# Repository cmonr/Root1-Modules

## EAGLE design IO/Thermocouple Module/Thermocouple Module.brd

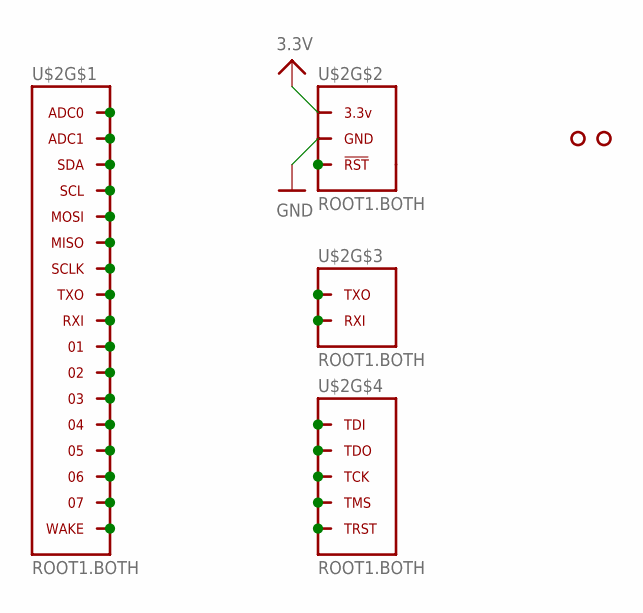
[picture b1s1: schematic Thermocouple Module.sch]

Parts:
U$2: ROOT1.BOTH
U$3, U$4: HOLE.2MM; 2MM

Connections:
3.3V: U$2.3.3V@1 (3.3V), U$2.3.3V@2 (3.3V), U$2.3.3V@3 (3.3V), U$2.3.3V@4 (3.3V), U$2.3.3V@5 (3.3V), U$2.3.3V@6 (3.3V), U$2.3.3V@7 (3.3V), U$2.3.3V@8 (3.3V), U$2.3.3V@9 (3.3V), U$2.3.3V@10 (3.3V), U$2.3.3V@11 (3.3V), U$2.3.3V@12 (3.3V), U$2.3.3V@13 (3.3V), U$2.3.3V@14 (3.3V), U$2.3.3V@15 (3.3V), U$2.3.3V@16 (3.3V), U$2.3.3V@17 (3.3V), U$2.3.3V@18 (3.3V), U$2.3.3V@19 (3.3V), U$2.3.3V@20 (3.3V), U$2.3.3V@21 (3.3V), U$2.3.3V@22 (3.3V), U$2.3.3V@23 (3.3V), U$2.3.3V@24 (3.3V), U$2.3.3V@VIA (3.3V)
GND: U$2.GND@1 (GND), U$2.GND@2 (GND), U$2.GND@3 (GND), U$2.GND@4 (GND), U$2.GND@5 (GND), U$2.GND@6 (GND), U$2.GND@7 (GND), U$2.GND@8 (GND), U$2.GND@9 (GND), U$2.GND@10 (GND), U$2.GND@11 (GND), U$2.GND@12 (GND), U$2.GND@13 (GND), U$2.GND@14 (GND), U$2.GND@15 (GND), U$2.GND@16 (GND), U$2.GND@17 (GND), U$2.GND@18 (GND), U$2.GND@19 (GND), U$2.GND@20 (GND), U$2.GND@21 (GND), U$2.GND@22 (GND), U$2.GND@23 (GND), U$2.GND@24 (GND), U$2.GND@25 (GND), U$2.GND@26 (GND), U$2.GND@VIA (GND)
unnamed: U$2.04, U$2.04@1 (04), U$2.04@VIA (04)
unnamed: U$2.ADC1, U$2.ADC1@1 (ADC1), U$2.ADC1@VIA (ADC1)
unnamed: U$2.SDA, U$2.SDA@1 (SDA), U$2.SDA@VIA (SDA)
unnamed: U$2.SCL, U$2.SCL@1 (SCL), U$2.SCL@VIA (SCL)
unnamed: U$2.03, U$2.03@1 (03), U$2.03@VIA (03)
unnamed: U$2.MISO, U$2.MISO@1 (MISO), U$2.MISO@VIA (MISO)
unnamed: U$2.SCLK, U$2.SCLK@1 (SCLK), U$2.SCLK@VIA (SCLK)
unnamed: U$2.TXO, U$2.TXO@1 (TXO), U$2.TXO@VIA (TXO)
unnamed: U$2.RXI, U$2.RXI@1 (RXI), U$2.RXI@VIA (RXI)
unnamed: U$2.01, U$2.01@1 (01), U$2.01@VIA (01)
unnamed: U$2.02, U$2.02@1 (02), U$2.02@VIA (02)
unnamed: U$2.MOSI, U$2.MOSI@1 (MOSI), U$2.MOSI@VIA (MOSI)
unnamed: U$2.ADC0, U$2.ADC0@1 (ADC0), U$2.ADC0@VIA (ADC0)
unnamed: U$2.05, U$2.05@1 (05), U$2.05@VIA (05)
unnamed: U$2.06, U$2.06@1 (06), U$2.06@VIA (06)
unnamed: U$2.07, U$2.07@1 (07), U$2.07@VIA (07)
unnamed: U$2.WAKE, U$2.WAKE@1 (WAKE), U$2.WAKE@VIA (WAKE)
unnamed: U$2.TDI, U$2.TDI@1 (TDI), U$2.TDI@VIA (TDI)
unnamed: U$2.TDO, U$2.TDO@1 (TDO), U$2.TDO@VIA (TDO)
unnamed: U$2.TCK, U$2.TCK@1 (TCK), U$2.TCK@VIA (TCK)
unnamed: U$2.TMS, U$2.TMS@1 (TMS), U$2.TMS@VIA (TMS)
unnamed: U$2.TRST, U$2.TRST@1 (TRST), U$2.TRST@VIA (TRST)
unnamed: U$2.RXI.DBG (RXI), U$2.RXI.DBG@1 (RXI), U$2.RXI.DBG@VIA (RXI)
unnamed: U$2.TXO.DBG (TXO), U$2.TXO.DBG@1 (TXO), U$2.TXO.DBG@VIA (TXO)
unnamed: U$2.RST (!RST), U$2.RST@1 (!RST), U$2.RST@VIA (!RST)

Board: 2 copper layers, 3 parts (0 on the bottom side), 27 nets, no tracks yet.

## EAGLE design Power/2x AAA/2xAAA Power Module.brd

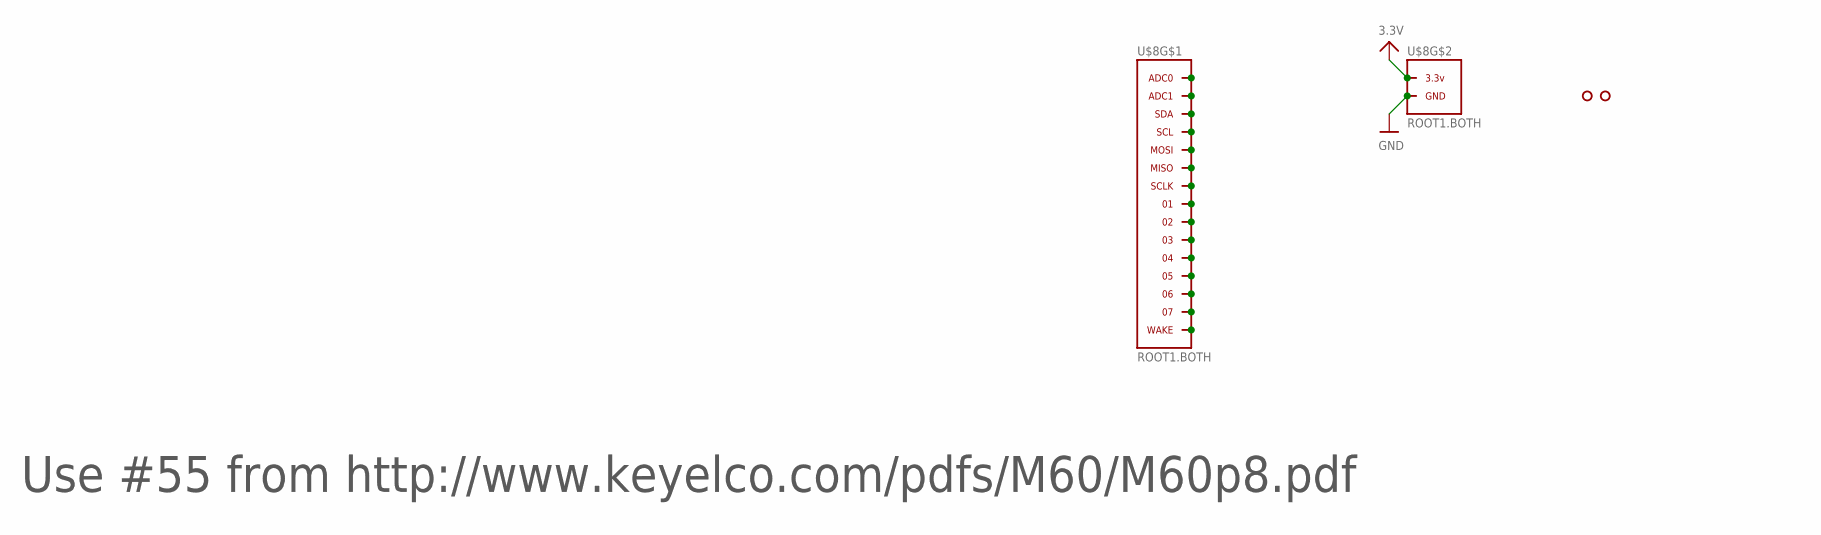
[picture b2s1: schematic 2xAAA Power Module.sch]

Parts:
U$3, U$4: HOLE.2MM; 2MM
U$8: ROOT1.BOTH

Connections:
3.3V: U$8.3.3V@1 (3.3V), U$8.3.3V@2 (3.3V), U$8.3.3V@3 (3.3V), U$8.3.3V@4 (3.3V), U$8.3.3V@5 (3.3V), U$8.3.3V@6 (3.3V), U$8.3.3V@7 (3.3V), U$8.3.3V@8 (3.3V), U$8.3.3V@9 (3.3V), U$8.3.3V@10 (3.3V), U$8.3.3V@VIA (3.3V)
GND: U$8.GND@1 (GND), U$8.GND@2 (GND), U$8.GND@3 (GND), U$8.GND@4 (GND), U$8.GND@5 (GND), U$8.GND@6 (GND), U$8.GND@7 (GND), U$8.GND@8 (GND), U$8.GND@9 (GND), U$8.GND@10 (GND), U$8.GND@11 (GND), U$8.GND@12 (GND), U$8.GND@13 (GND), U$8.GND@14 (GND), U$8.GND@15 (GND), U$8.GND@16 (GND), U$8.GND@17 (GND), U$8.GND@18 (GND), U$8.GND@19 (GND), U$8.GND@20 (GND), U$8.GND@VIA (GND)
unnamed: U$8.ADC0, U$8.ADC0@1 (ADC0), U$8.ADC0@VIA (ADC0)
unnamed: U$8.ADC1, U$8.ADC1@1 (ADC1), U$8.ADC1@VIA (ADC1)
unnamed: U$8.SDA, U$8.SDA@1 (SDA), U$8.SDA@VIA (SDA)
unnamed: U$8.SCL, U$8.SCL@1 (SCL), U$8.SCL@VIA (SCL)
unnamed: U$8.MOSI, U$8.MOSI@1 (MOSI), U$8.MOSI@VIA (MOSI)
unnamed: U$8.MISO, U$8.MISO@1 (MISO), U$8.MISO@VIA (MISO)
unnamed: U$8.SCLK, U$8.SCLK@1 (SCLK), U$8.SCLK@VIA (SCLK)
unnamed: U$8.01, U$8.01@1 (01), U$8.01@VIA (01)
unnamed: U$8.02, U$8.02@1 (02), U$8.02@VIA (02)
unnamed: U$8.03, U$8.03@1 (03), U$8.03@VIA (03)
unnamed: U$8.04, U$8.04@1 (04), U$8.04@VIA (04)
unnamed: U$8.05, U$8.05@1 (05), U$8.05@VIA (05)
unnamed: U$8.06, U$8.06@1 (06), U$8.06@VIA (06)
unnamed: U$8.07, U$8.07@1 (07), U$8.07@VIA (07)
unnamed: U$8.WAKE, U$8.WAKE@1 (WAKE), U$8.WAKE@VIA (WAKE)

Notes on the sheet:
Use #55 from http://www.keyelco.com/pdfs/M60/M60p8.pdf

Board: 2 copper layers, 3 parts (0 on the bottom side), 17 nets, no tracks yet.

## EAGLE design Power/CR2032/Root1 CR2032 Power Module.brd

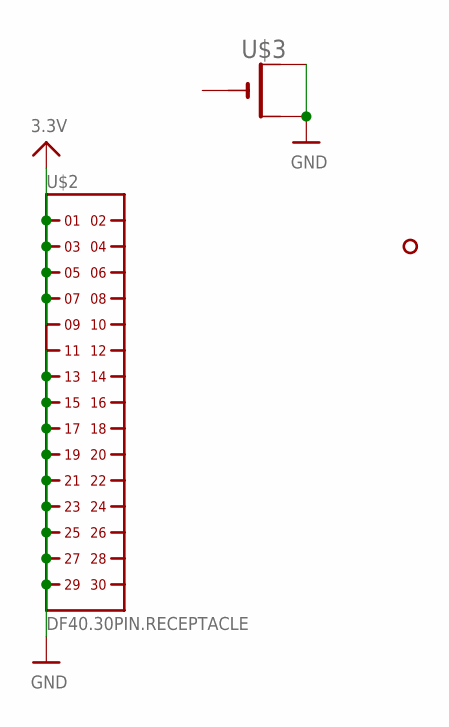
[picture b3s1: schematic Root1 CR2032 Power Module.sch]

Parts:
U$2: DF40.30PIN.RECEPTACLE; DF40(XX)-30DS-0.4V
U$3: CR2032THM; CR2032-THRU
U$4: HOLE.4MM; 4MM

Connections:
3.3V: U$2.1, U$2.3, U$2.5, U$2.7, U$2.9
GND: U$2.11, U$2.13, U$2.15, U$2.17, U$2.19, U$2.21, U$2.23, U$2.25, U$2.27, U$2.29, U$3.+1 (+), U$3.+2 (+1)

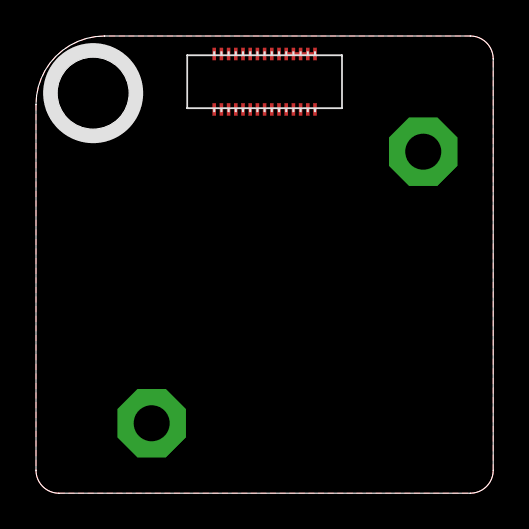
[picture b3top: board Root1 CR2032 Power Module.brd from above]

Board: 2 copper layers, 25.4 x 25.4 mm, 3 parts (1 on the bottom side), 2 nets.

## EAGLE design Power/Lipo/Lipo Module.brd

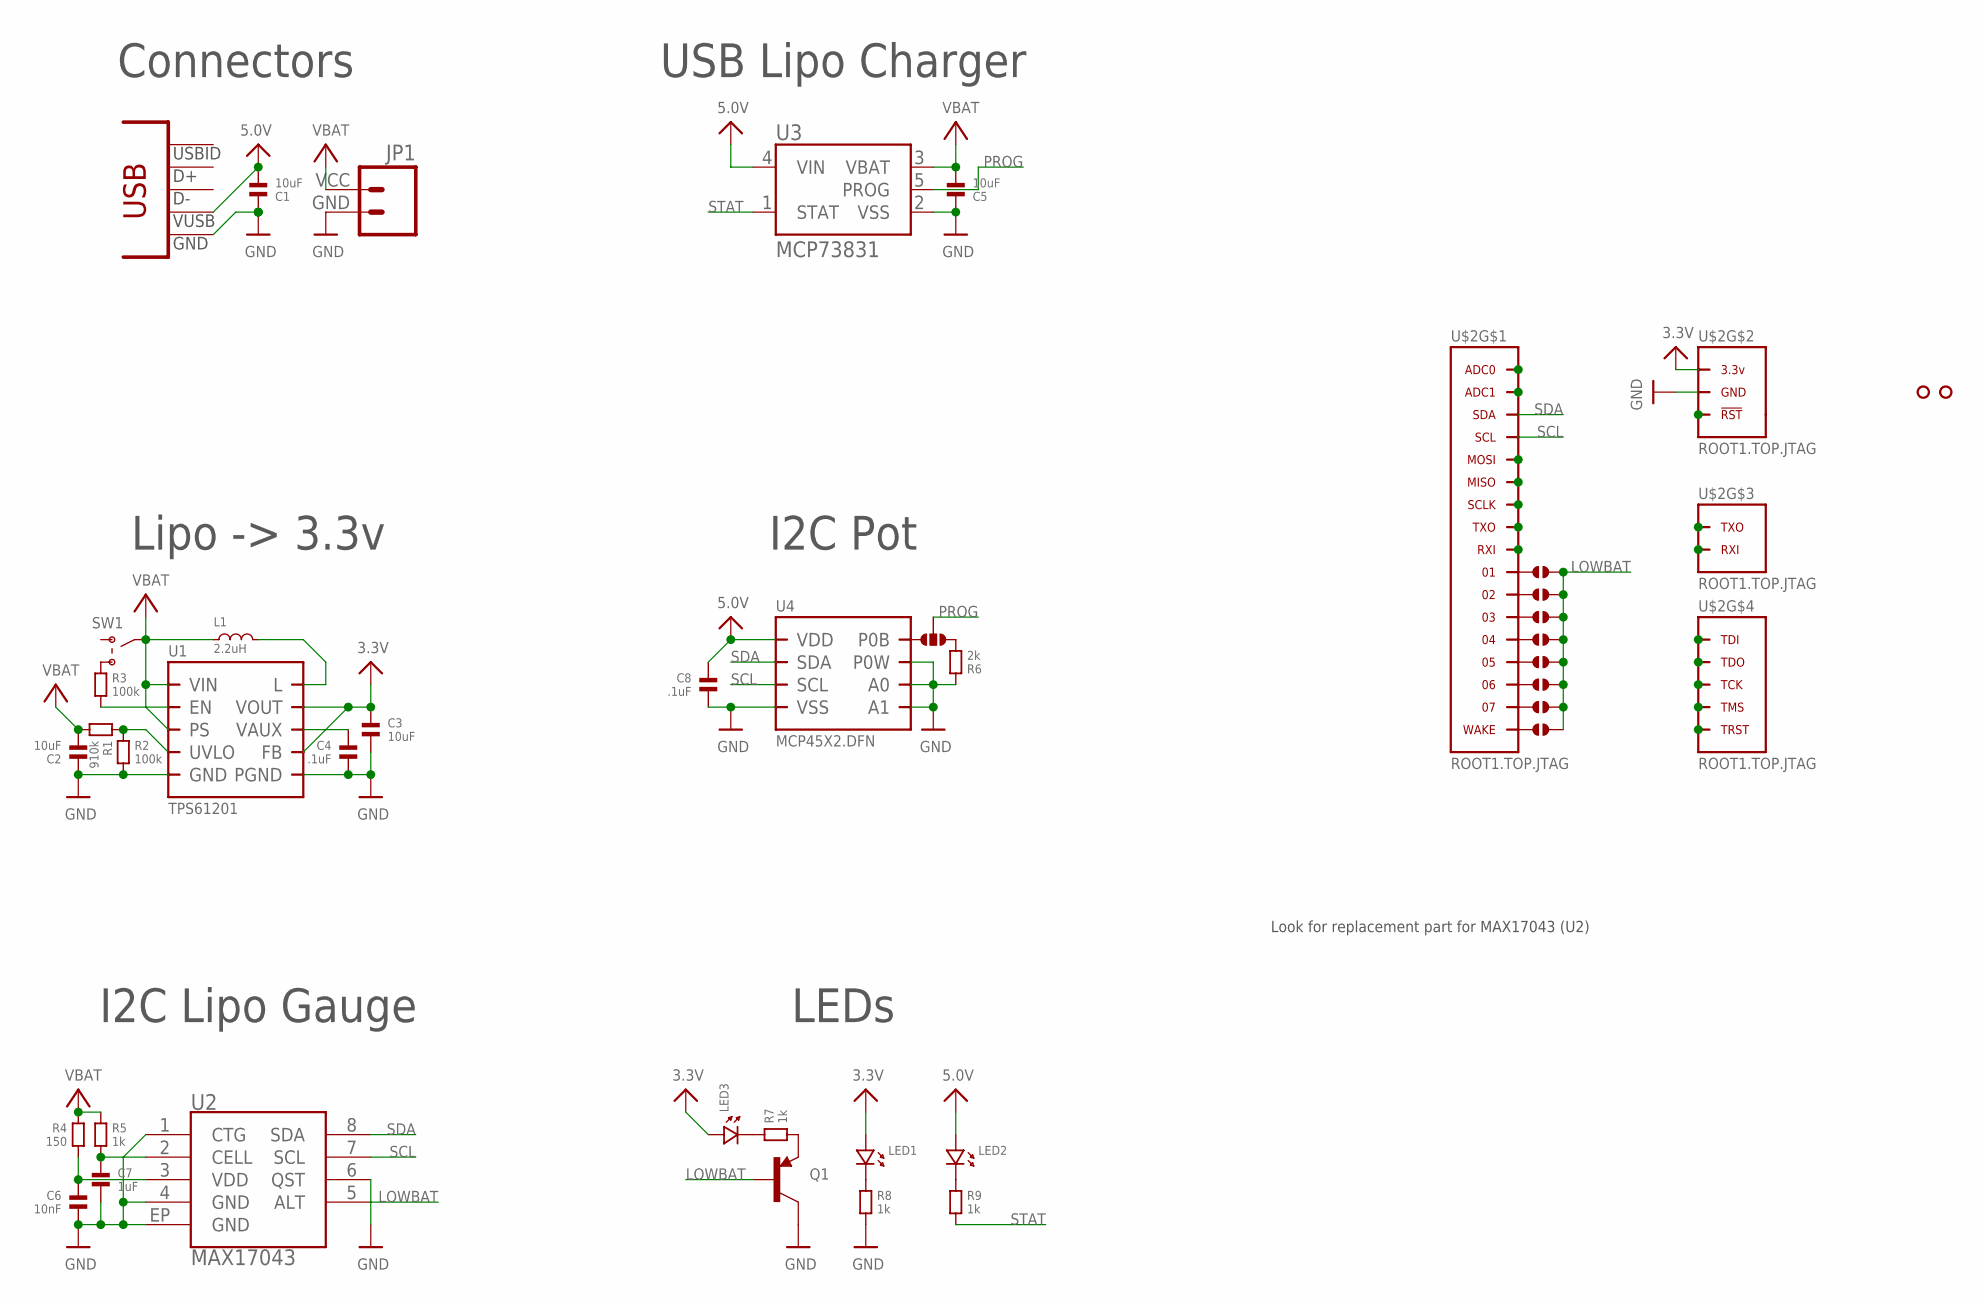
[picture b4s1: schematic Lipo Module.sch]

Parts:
C1, C2, C3, C5: 10uF; 0805
C4, C8: .1uF; 0603
C6: 10nF; 0603
C7: 1uF; 0603
J1: SOLDERJUMPER.3.LRG.23; 3.LRG.23
J2, J3, J4, J5, J6, J7, J8, J9: SOLDERJUMPER.2.SML; 2.SML
JP1: M024UCON-15767; JST-2-SMD-VERT
L1: 2.2uH; SRN3015
LED1, LED2, LED3: LED.0603; 0603.LED
Q1: TRANSISTOR_PNPSOT23-REFLOW; SOT23-R
R1: 910k; 0603
R2, R3: 100k; 0603
R4: 150; 0603
R5, R7, R8, R9: 1k; 0603
R6: 2k; 0603
SW1: SSSS810701
U1: TPS61201; DRC
U2: MAX17043; TDFN-8
U3: MCP73831; SOT23-5
U4: MCP45X2.DFN; DFN-8.3X3.PAD
U$2: ROOT1.TOP.JTAG; ROOT1.TOP
U$3, U$4: HOLE.2MM; 2MM
USB1: CON-USB-F-MICRO-B; CONN_USB_MICRO-B

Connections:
3.3V: C3.1, LED1.P$1 (1), LED3.P$1 (1), U1.2 (VOUT), U1.10 (FB), U$2.3.3V@1 (3.3V), U$2.3.3V@2 (3.3V), U$2.3.3V@3 (3.3V), U$2.3.3V@4 (3.3V), U$2.3.3V@5 (3.3V), U$2.3.3V@6 (3.3V), U$2.3.3V@7 (3.3V), U$2.3.3V@8 (3.3V), U$2.3.3V@9 (3.3V), U$2.3.3V@10 (3.3V), U$2.3.3V@11 (3.3V), U$2.3.3V@12 (3.3V)
5.0V: C1.2, C8.1, LED2.P$1 (1), U3.4 (VIN), U4.8 (VDD), USB1.P1 (VUSB)
GND: C1.1, C2.1, C3.2, C4.2, C5.1, C6.2, C7.2, C8.2, JP1.GND (1), Q1.3 (C), R2.2, R6.1, R8.2, U1.4 (PGND), U1.9 (GND), U1.PAD (PGND), U2.1 (CTG), U2.4 (GND), U2.6 (QST), U2.EP (GND), U3.2 (VSS), U4.1 (A0), U4.4 (VSS), U4.5 (P0W), U4.7 (A1), U4.PAD (VSS), U$2.GND@1 (GND), U$2.GND@2 (GND), U$2.GND@3 (GND), U$2.GND@4 (GND), U$2.GND@5 (GND), U$2.GND@6 (GND), U$2.GND@7 (GND), U$2.GND@8 (GND), U$2.GND@9 (GND), U$2.GND@10 (GND), U$2.GND@11 (GND), U$2.GND@12 (GND), U$2.GND@13 (GND), USB1.P5 (GND)
LOWBAT: J2.2, J3.2, J4.2, J5.2, J6.2, J7.2, J8.2, J9.2, Q1.1 (B), U2.5 (ALT)
unnamed: J2.1, U$2.01
unnamed: LED2.P$2 (2), R9.1
unnamed: L1.2, U1.3 (L)
unnamed: J3.1, U$2.02
unnamed: J4.1, U$2.03
unnamed: J5.1, U$2.04
unnamed: J6.1, U$2.05
unnamed: J7.1, U$2.06
unnamed: J8.1, U$2.07
unnamed: J9.1, U$2.WAKE
unnamed: R3.1, SW1.1 (B)
unnamed: C6.1, R4.2, U2.3 (VDD)
unnamed: C7.1, R5.2, U2.2 (CELL)
unnamed: J1.1, U4.6 (P0B)
unnamed: J1.3, R6.2
unnamed: LED1.P$2 (2), R8.1
unnamed: R3.2, U1.6 (EN)
unnamed: Q1.2 (E), R7.2
unnamed: LED3.P$2 (2), R7.1
unnamed: C4.1, U1.1 (VAUX)
unnamed: R1.1, R2.1, U1.7 (UVLO)
PROG: J1.2, U3.5 (PROG)
SCL: U2.7 (SCL), U4.2 (SCL), U$2.SCL
SDA: U2.8 (SDA), U4.3 (SDA), U$2.SDA
STAT: R9.2, U3.1 (STAT)
VBAT: C2.2, C5.2, JP1.VCC (2), L1.1, R1.2, R4.1, R5.1, SW1.2 (COM), U1.5 (VIN), U1.8 (PS), U3.3 (VBAT)

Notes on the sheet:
USB Lipo Charger
I2C Lipo Gauge
Lipo -> 3.3v
Connectors
I2C Pot
LEDs
Look for replacement part for MAX17043 (U2)

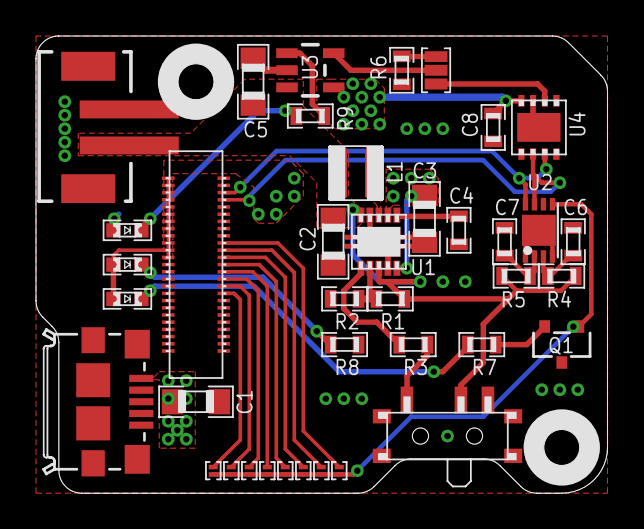
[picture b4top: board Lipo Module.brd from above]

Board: 2 copper layers, 31.8 x 25.4 mm, 41 parts (0 on the bottom side), 30 nets.

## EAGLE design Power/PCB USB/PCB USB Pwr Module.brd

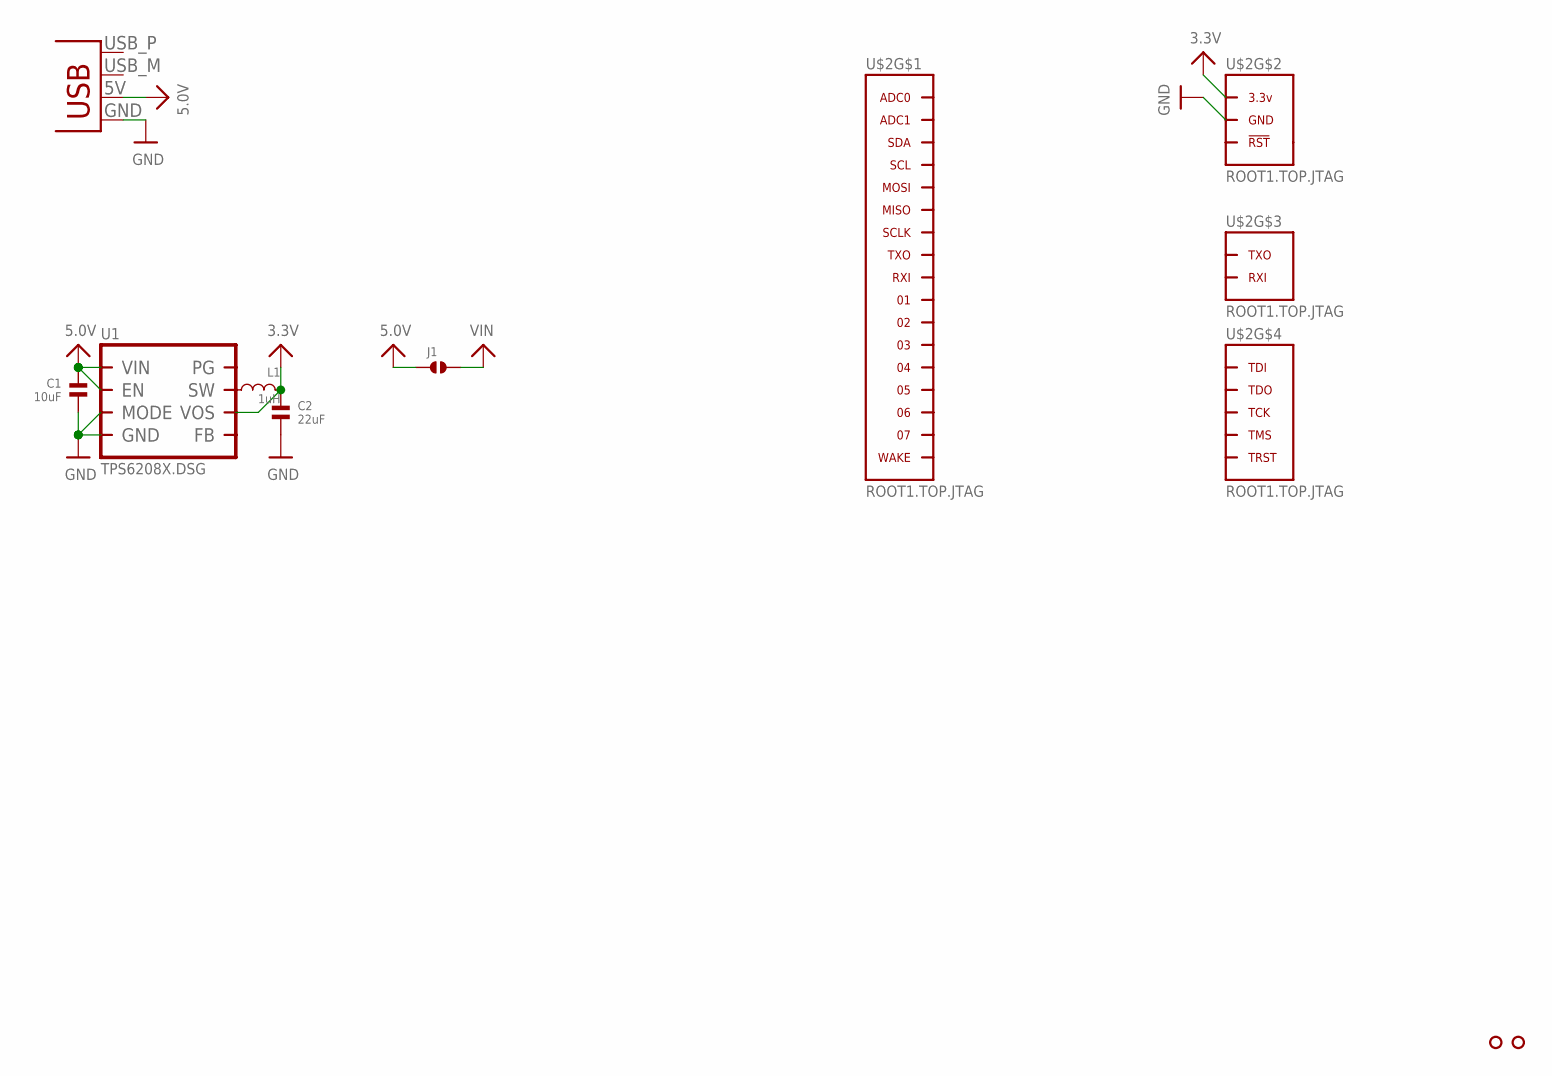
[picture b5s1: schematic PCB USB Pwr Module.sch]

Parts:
C1: 10uF; 0603
C2: 22uF; 0805
J1: SOLDERJUMPER.2.LRG.PASTE; 2.LRG.PASTE
JP1: USBPCB; USB-A-PCB
L1: 1uH; SRN3015
U1: TPS6208X.DSG; DSG
U$2: ROOT1.TOP.JTAG; ROOT1.TOP
U$3, U$4: HOLE.#2; #2

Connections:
3.3V: C2.1, L1.1, U1.5 (VOS), U$2.3.3V@1 (3.3V), U$2.3.3V@2 (3.3V), U$2.3.3V@3 (3.3V), U$2.3.3V@4 (3.3V), U$2.3.3V@5 (3.3V), U$2.3.3V@6 (3.3V), U$2.3.3V@7 (3.3V), U$2.3.3V@8 (3.3V), U$2.3.3V@9 (3.3V), U$2.3.3V@10 (3.3V), U$2.3.3V@11 (3.3V), U$2.3.3V@12 (3.3V)
5.0V: C1.1, J1.1, JP1.5V (VBUS), U1.1 (EN), U1.8 (VIN)
GND: C1.2, C2.2, JP1.GND, U1.2 (GND), U1.3 (MODE), U1.PAD (GND), U$2.GND@1 (GND), U$2.GND@2 (GND), U$2.GND@3 (GND), U$2.GND@4 (GND), U$2.GND@5 (GND), U$2.GND@6 (GND), U$2.GND@7 (GND), U$2.GND@8 (GND), U$2.GND@9 (GND), U$2.GND@10 (GND), U$2.GND@11 (GND), U$2.GND@12 (GND), U$2.GND@13 (GND)
unnamed: L1.2, U1.7 (SW)
VIN: J1.2

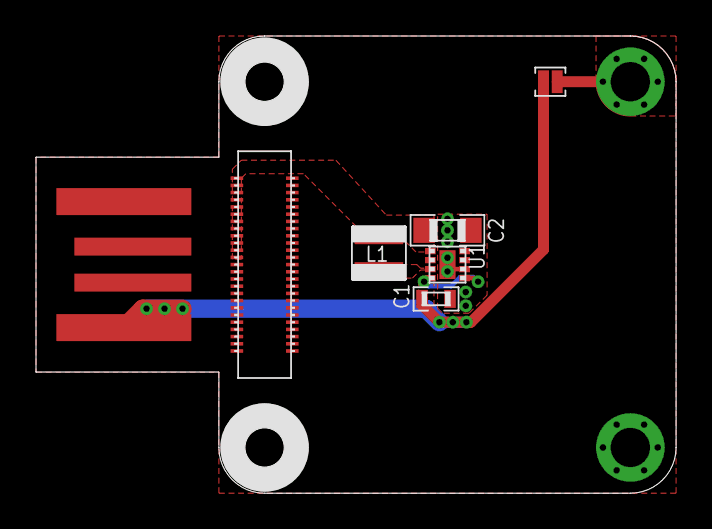
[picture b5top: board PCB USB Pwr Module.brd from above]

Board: 2 copper layers, 35.6 x 25.4 mm, 9 parts (0 on the bottom side), 4 nets.

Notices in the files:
parts and their libraries:
SparkFun-Connectors: Licensing: CC v3.0 Share-Alike You are welcome to use this library for commercial purposes.
